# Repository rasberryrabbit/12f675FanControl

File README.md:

# 12f675FanControl
12F675 Fan Control with thermistor

it use soft PWM and make some noise.

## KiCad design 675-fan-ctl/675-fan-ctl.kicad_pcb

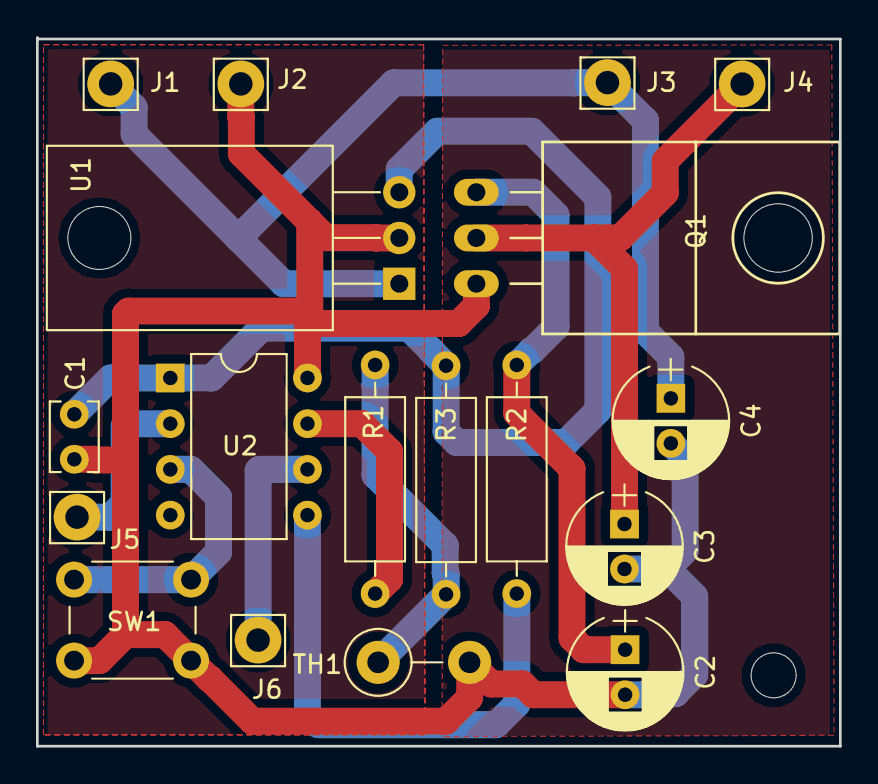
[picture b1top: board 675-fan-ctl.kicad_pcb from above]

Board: 2 copper layers, 44.6 x 39.4 mm, 18 parts (0 on the bottom side), 11 nets.

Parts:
C1: 0.1u; C_Disc_D3.8mm_W2.6mm_P2.50mm
C2, C3: 1u; CP_Radial_D6.3mm_P2.50mm
C4: 47u; CP_Radial_D6.3mm_P2.50mm
J1: +; Pin_d1.4mm_L8.5mm_W2.8mm_FlatFork
J2: -; Pin_d1.4mm_L8.5mm_W2.8mm_FlatFork
J3: M+; Pin_d1.4mm_L8.5mm_W2.8mm_FlatFork
J4: M-; Pin_d1.4mm_L8.5mm_W2.8mm_FlatFork
J5, J6: Conn_01x01_Male; Pin_d1.4mm_L8.5mm_W2.8mm_FlatFork
Q1: 3055T; TO-220_Neutral123_Horizontal
R1: 10k; R_Axial_DIN0309_L9.0mm_D3.2mm_P12.70mm_Horizontal
R2: 4.7k; R_Axial_DIN0309_L9.0mm_D3.2mm_P12.70mm_Horizontal
R3: 2.2k; R_Axial_DIN0309_L9.0mm_D3.2mm_P12.70mm_Horizontal
SW1: High Spin; SW_PUSH_6mm
TH1: NTC-502F397; R_Axial_DIN0411_L9.9mm_D3.6mm_P5.08mm_Vertical
U1: LM7805_TO220; TO-220-3_Horizontal
U2: PIC12F675-IP; DIP-8_W7.62mm

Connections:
GND: C1.2, C2.2, C3.2, C4.2, J2.1, Q1.3, SW1.1, TH1.2, U1.2, U2.8
unnamed: C1.1, R3.2, U1.3, U2.1
unnamed: C2.1, Q1.1, R2.1
unnamed: C3.1, J4.1, Q1.2
unnamed: J5.1, U2.2
unnamed: J6.1, U2.6
unnamed: R1.1, U2.7
unnamed: R1.2, R3.1, TH1.1
unnamed: R2.2, U2.5
unnamed: SW1.2, U2.3
VCC: C4.1, J1.1, J3.1, U1.1

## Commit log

2018-08-15 first
2018-08-15 add calc table.
2018-08-15 small changes.
2018-08-16 add capacitor.
